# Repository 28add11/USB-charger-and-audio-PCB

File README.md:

# USB charger and audio PCB
 A PCB with decently fast USB charging and audio playback support

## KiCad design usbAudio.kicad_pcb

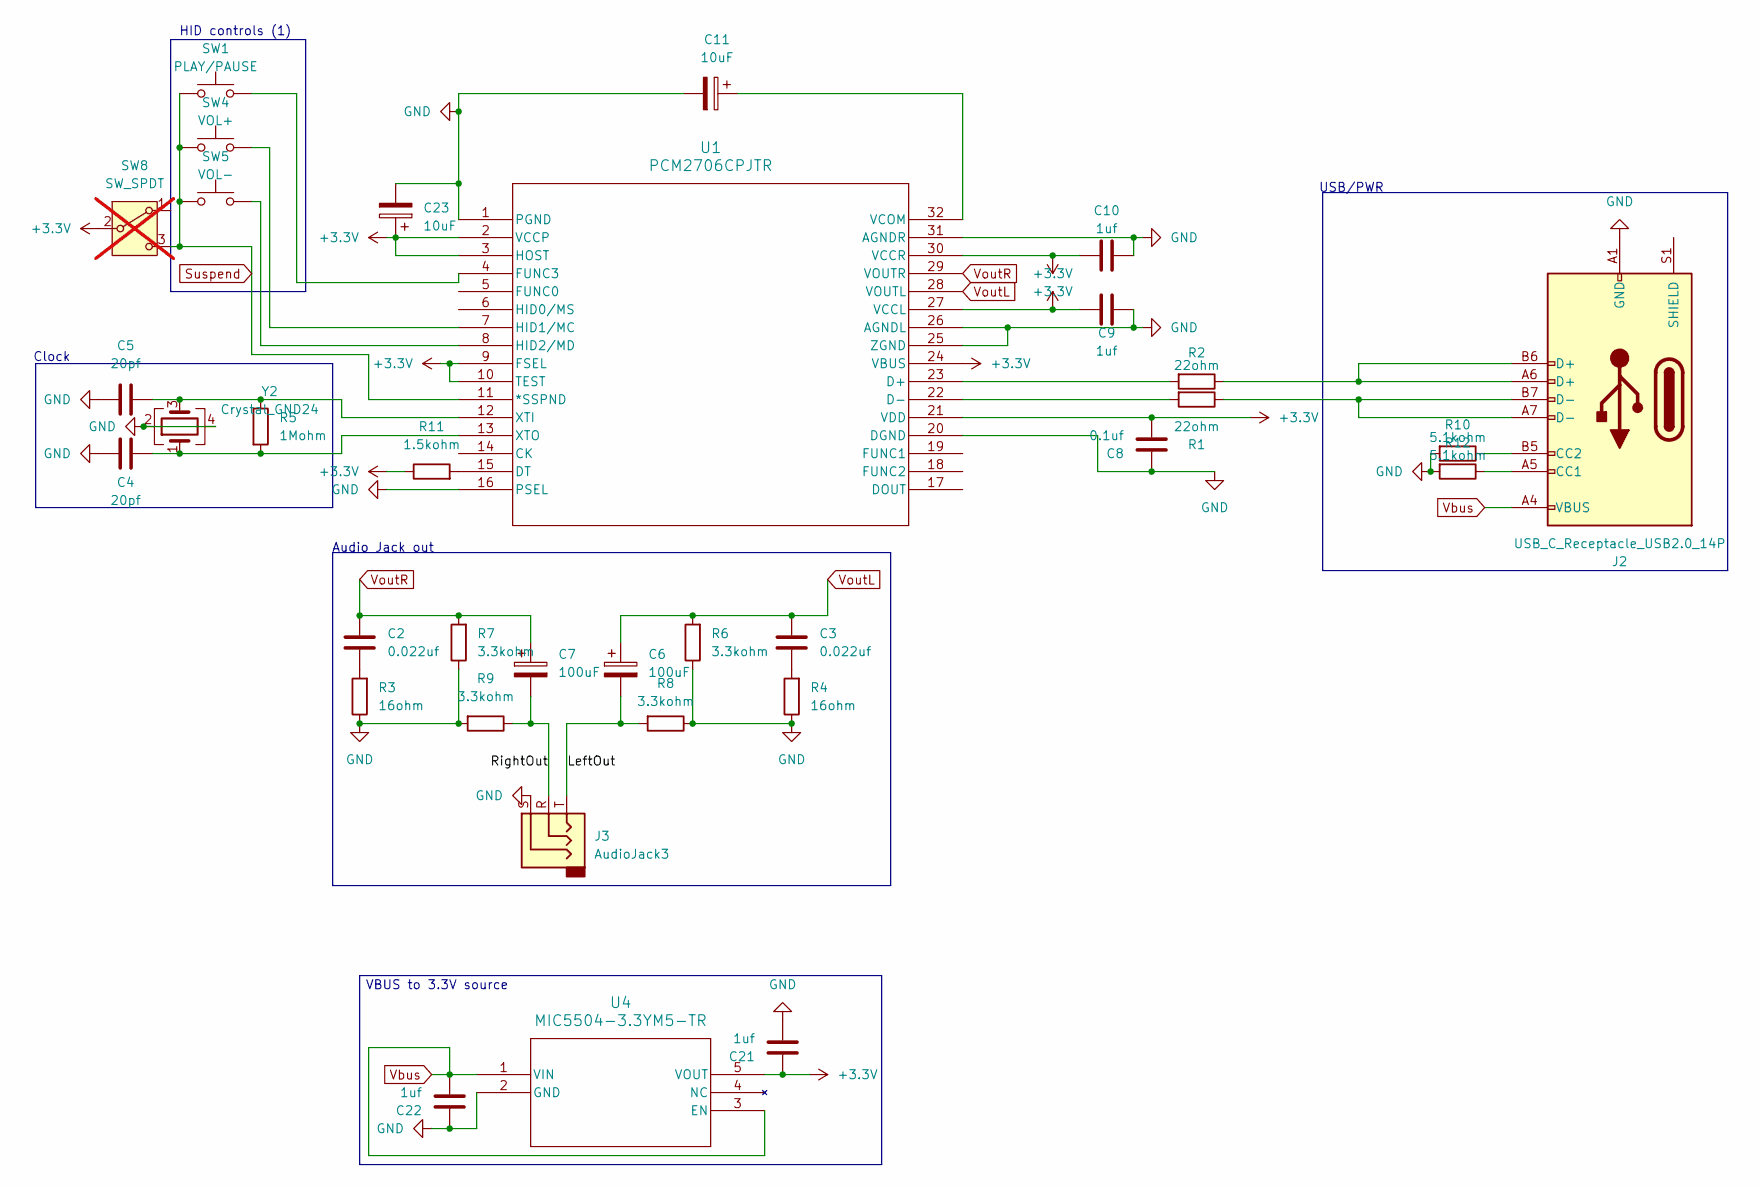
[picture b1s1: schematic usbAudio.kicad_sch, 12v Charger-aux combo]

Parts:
C2, C3: 0.022uf; C_0805_2012Metric_Pad1.18x1.45mm_HandSolder; LCSC Part # C107147
C4, C5: 20pf; C_0603_1608Metric_Pad1.08x0.95mm_HandSolder; LCSC Part # C105621
C6, C7: 100uF; CP_Radial_D6.3mm_P2.50mm; LCSC Part # C109392
C8: 0.1uf; C_0603_1608Metric_Pad1.08x0.95mm_HandSolder; LCSC Part # C14663
C9, C10, C21, C22: 1uf; C_0603_1608Metric_Pad1.08x0.95mm_HandSolder; LCSC Part # C1592
C11, C23: 10uF; CP_Radial_D5.0mm_P2.00mm; LCSC Part # C250876
J2: USB_C_Receptacle_USB2.0_14P; USB_C_Receptacle_HCTL_HC-TYPE-C-16P-01A; LCSC Part # C2894897
J3: AudioJack3; Jack_3.5mm_KoreanHropartsElec_PJ-320D-4A_Horizontal_copy; LCSC Part # C95562
R1, R2: 22ohm; R_0603_1608Metric_Pad0.98x0.95mm_HandSolder; LCSC Part # C23345
R3, R4: 16ohm; R_0603_1608Metric_Pad0.98x0.95mm_HandSolder; LCSC Part # C25185
R5: 1Mohm; R_0603_1608Metric_Pad0.98x0.95mm_HandSolder; LCSC Part # C22935
R6, R7, R8, R9: 3.3kohm; R_0603_1608Metric_Pad0.98x0.95mm_HandSolder; LCSC Part # C22978
R10, R12: 5.1kohm; R_0603_1608Metric_Pad0.98x0.95mm_HandSolder; LCSC Part # C23186
R11: 1.5kohm; R_0603_1608Metric_Pad0.98x0.95mm_HandSolder; LCSC Part # C22843
SW1: PLAY/PAUSE; SW_PUSH_6mm_H4.3mm; LCSC Part # C97440
SW4: VOL+; SW_PUSH_6mm_H4.3mm; LCSC Part # C97440
SW5: VOL-; SW_PUSH_6mm_H4.3mm; LCSC Part # C97440
SW8: SW_SPDT; SW_JS102011SAQN_Xoverhang; not fitted
U1: PCM2706CPJTR; PJT32; LCSC Part # C2651268
U4: MIC5504-3.3YM5-TR; SOT-23-5_MC_MCH; LCSC Part # C88419
Y2: Crystal_GND24; Crystal_SMD_3225-4Pin_3.2x2.5mm_HandSoldering; LCSC Part # C9002

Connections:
+3.3V: C8.1, C9.1, C10.1, C21.2, C23.1, R11.1, SW8.2 (B), U1.2 (VCCP), U1.3 (HOST), U1.9 (FSEL), U1.10 (TEST), U1.21 (VDD), U1.24 (VBUS), U1.27 (VCCL), U1.30 (VCCR), U4.5 (VOUT)
/LeftOut: C6.2, J3.T, R8.2
/RightOut: C7.2, J3.R, R9.1
GND: C4.2, C5.2, C8.2, C9.2, C10.2, C11.2, C21.1, C22.2, C23.2, J2.A1 (GND), J2.A12 (GND), J2.B1 (GND), J2.B12 (GND), J3.S, R3.1, R4.1, R6.1, R7.1, R8.1, R9.2, R10.2, R12.2, U1.1 (PGND), U1.16 (PSEL), U1.20 (DGND), U1.25 (ZGND), U1.26 (AGNDL), U1.31 (AGNDR), U4.2 (GND), Y2.2, Y2.4
unnamed: C2.1, R3.2
unnamed: C3.1, R4.2
unnamed: J2.A5 (CC1), R12.1
unnamed: J2.B5 (CC2), R10.1
unnamed: J2.A6 (D+), J2.B6 (D+), R2.1
unnamed: J2.A7 (D-), J2.B7 (D-), R1.1
unnamed: R2.2, U1.23 (D+)
unnamed: R1.2, U1.22 (D-)
unnamed: R11.2, U1.15 (DT)
unnamed: SW1.2, U1.4 (FUNC3)
unnamed: SW4.2, U1.7 (HID1/MC)
unnamed: SW5.2, U1.8 (HID2/MD)
unnamed: C11.1, U1.32 (VCOM)
unnamed: C5.1, R5.1, U1.12 (XTI), Y2.3
unnamed: C4.1, R5.2, U1.13 (XTO), Y2.1
Suspend: SW1.1, SW4.1, SW5.1, SW8.3 (C), U1.11 (*SSPND)
Vbus: C22.1, J2.A4 (VBUS), J2.A9 (VBUS), J2.B4 (VBUS), J2.B9 (VBUS), U4.1 (VIN), U4.3 (EN)
VoutL: C3.2, C6.1, R6.2, U1.28 (VOUTL)
VoutR: C2.2, C7.1, R7.2, U1.29 (VOUTR)

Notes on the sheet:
USB/PWR
HID controls (1)
Audio Jack out
Clock
VBUS to 3.3V source

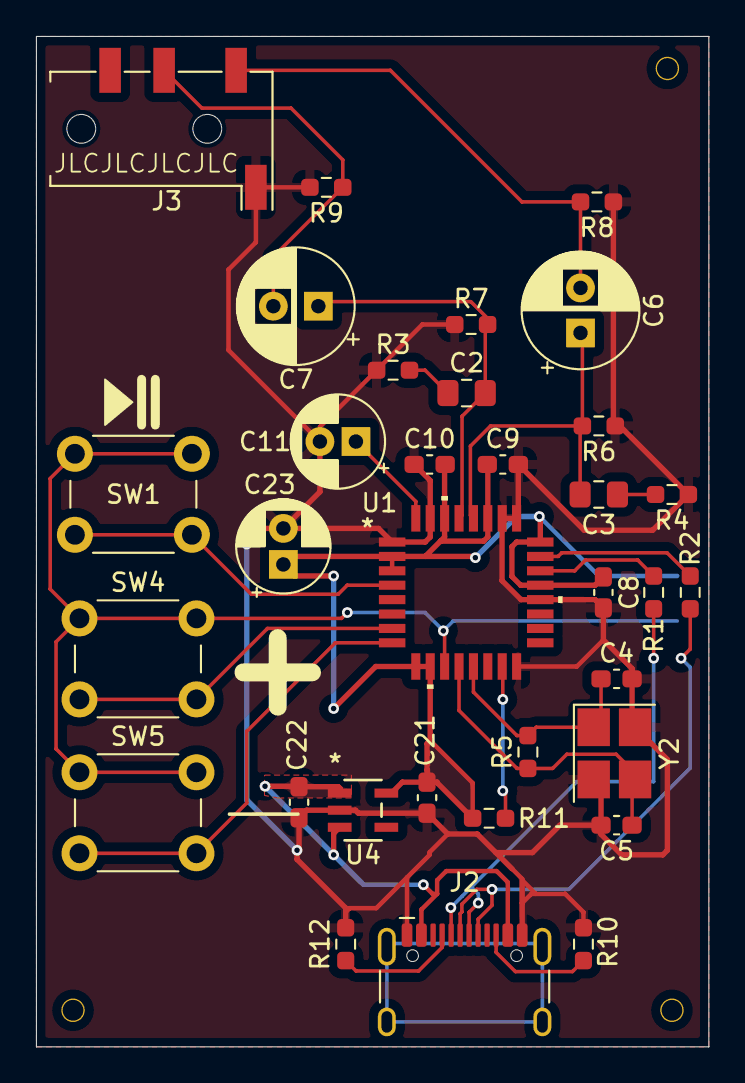
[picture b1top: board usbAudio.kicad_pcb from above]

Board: 2 copper layers, 37.4 x 56.1 mm, 34 parts (1 on the bottom side), 23 nets.

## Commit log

2024-08-19 Start schematic
2024-08-19 Work on setting up audio IC
2024-08-19 Finish audio IC
2024-08-19 Start work on power side
2024-08-19 Finish schem!
2024-08-20 Cleaning up and adding footprints
2024-08-20 Start work on PCB itself
2024-08-21 Layout time!!!
2024-08-21 Make more dense!!!!
2024-08-21 Made ready for production!
